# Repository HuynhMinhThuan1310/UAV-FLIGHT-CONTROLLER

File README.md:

# 🚁 UAV Quadcopter Flight Controller & Telemetry System

Hệ thống điều khiển bay (Flight Controller) và trạm thu phát dữ liệu từ xa (Ground Station) hoàn chỉnh cho máy bay không người lái (UAV Quadcopter), bao gồm đầy đủ **Phần cứng (PCB KiCad)**, **Firmware điều khiển bay (STM32CubeIDE)**, và **Firmware trạm thu dữ liệu (ESP32-C3 ESP-IDF)**.

---

## 📌 Cấu Trúc Dự Án (Repository Structure)

```text
uav_ground_station/
├── mach-UAV-main/                    # Firmware STM32CubeIDE cho máy bay
│   └── firmware/
│       ├── uav_complete_fc/          # >> Firmware điều khiển bay hoàn chỉnh (Quad Flight Controller)
│       ├── doccambien/               # Module đọc và kiểm thử cảm biến (IMU MPU6050, Khí áp, La bàn)
│       ├── DocRF/                    # Module giao tiếp vô tuyến nRF24L01+
│       └── PWM_ADC_TIMER/            # Module đọc PWM tay cầm, đo điện áp pin ADC và Timer
├── thiet_ke_mach/                    # Thiết kế phần cứng mạch PCB (KiCad 10)
│   ├── mach_uav.kicad_sch            # Sơ đồ nguyên lý (Schematic)
│   ├── mach_uav.kicad_pcb            # Mạch in hoàn chỉnh (Layout 92x92mm)
│   ├── HUONG_DAN_DI_DAY_NGOAI.md     # Sơ đồ cầu nối ngoài (W1-W6) cho mạch 1 lớp
│   ├── mach_uav-*.gbr                # Bộ file Gerber sản xuất mạch in
│   └── *.pretty / ZC323000/          # Thư viện footprint linh kiện tùy chỉnh
└── main/                             # Firmware trạm mặt đất Ground Station (ESP32-C3)
    ├── main.c                        # FreeRTOS tasks giải mã telemetry và log Serial Monitor
    ├── nrf24_rx.c / nrf24_rx.h       # Driver SPI cho nRF24L01+ ở tần số 2.480 GHz
    └── telemetry_protocol.h          # Giao thức truyền tin nhị phân 32 byte + CRC-8
```

---

## 1. Firmware Điều Khiển Bay STM32 (`mach-UAV-main/firmware/uav_complete_fc`)

Dự án phát triển trên **STM32CubeIDE** cho vi điều khiển **STM32F103C8T6 (ARM Cortex-M3 @ 72 MHz HSE)**:

- **Chế độ bay (Flight Mode):** Cố định chế độ cân bằng góc (`ANGLE Mode`) kết hợp tự động bù góc nghiêng.
- **Vòng lặp điều khiển PID:** Bộ điều khiển PID độc lập cho 3 trục Roll, Pitch, Yaw với:
  - Tích hợp bộ lọc đạo hàm (`d_filter`).
  - Khử bão hòa tích phân (Anti-windup Integrator Limit).
  - Giới hạn ngõ ra an toàn (`output_limit`).
- **Xử lý cảm biến góc nghiêng & La bàn (GY-87):**
  - Giao tiếp cảm biến `MPU6050` (Gyro + Accel) qua **Hardware I2C1 (`PB6/PB7`)** được cấu hình thanh ghi trực tiếp, tránh trễ và lỗi bus của thư viện HAL.
  - Tích hợp la bàn số `HMC5883L` sửa trôi góc Yaw theo thời gian thực (loại bỏ nhiễu từ trường khi dòng tải động cơ thay đổi đột ngột).
- **Giữ hướng bay (Heading Hold):** Khóa hướng tham chiếu (`REF`) bằng tích phân con quay hồi chuyển, duy trì mũi máy bay ổn định khi buông cần lái Yaw.
- **Đọc tín hiệu điều khiển RC (PWM Input Capture):**
  - 4 kênh PWM trên Timer `TIM3` (Roll: `PA6`, Pitch: `PA7`, Throttle: `PB0`, Yaw: `PB1`).
  - Khóa/Mở khóa động cơ bằng tổ hợp cần lái an toàn:
    - **Arm:** `Ga thấp + Gạt hết Yaw sang Phải trong 3s`.
    - **Disarm:** `Ga thấp + Gạt hết Yaw sang Trái trong 3s`.
- **Ngõ ra điều khiển động cơ (ESC Outputs):**
  - 4 kênh xung PWM độc lập (1000 - 2000 µs) trên Timer `TIM2` (`PA0`, `PA1`, `PA2`, `PA3`) bố trí theo layout quad X (`M1-M4`).
- **Cơ chế an toàn Failsafe đa cấp (`FailsafeMode`):**
  - Tự động phát hiện mất sóng vô tuyến hoặc mất xung PWM máy thu: Chuyển sang giữ thăng bằng (`HOLD`) $\rightarrow$ hạ độ cao từ từ (`DESCEND`) $\rightarrow$ phục hồi nếu có lại sóng (`RECOVER`).
  - Tự động ngắt khẩn cấp (Emergency Disarm) nếu cảm biến IMU bị lỗi liên tục.

---

## 2. Thiết Kế Mạch PCB Flight Controller (`thiet_ke_mach/`)

- **Kích thước & Thiết kế:** Bo mạch tiêu chuẩn **92 × 92 mm**, thiết kế trên **KiCad 10**.
- **Khối nguồn:** Bộ nguồn xung buck converter **MP1584EN** hạ áp từ pin LiPo cấp dòng khỏe **5V BEC**, kết hợp LDO **3.3V** riêng cho cảm biến và radio để chống sụt áp khi 4 động cơ hoạt động hết công suất.
- **Tối ưu hóa mạch 1 lớp & Giải pháp đi dây ngoài:**
  - Thiết kế mạch 1 lớp trên mặt đáy (`B.Cu`) không dùng via xuyên tầng, tối ưu cho gia công nhanh bằng phay CNC hoặc ăn mòn hóa học.
  - Định tuyến thông minh tối ưu hóa độ rộng đường mạch (Power trace 30–35 mil, Signal 14 mil, Clearance 0.20 mm).
  - Tối ưu 6 cầu nối ngoài (**W1 – W6**) có in nhãn hướng dẫn rõ ràng trực tiếp trên lớp lụa `F.SilkS` ([`HUONG_DAN_DI_DAY_NGOAI.md`](file:///C:/uav_ground_station/thiet_ke_mach/HUONG_DAN_DI_DAY_NGOAI.md)).
  - Phủ đồng mass `GND` diện tích lớn giúp tản nhiệt và chống nhiễu vô tuyến.

---

## 3. Firmware Trạm Thu Mặt Đất ESP32-C3 (`main/`)

- **Framework & RTOS:** Viết bằng native **ESP-IDF (v5.x/v6.x)** chạy trên nhân RISC-V của **ESP32-C3** với hệ điều hành thời gian thực **FreeRTOS**.
- **Giao thức Telemetry tốc độ cao (100 Hz):**
  - Gói tin nhị phân định dạng cố định **32 byte**, bảo vệ toàn vẹn bằng **CRC-8** (đa thức $0x07$).
  - Truyền nhận các khung: Góc nghiêng Roll/Pitch/Heading (`0xA1`), Vị trí cần lái RC (`0xA2`), Trạng thái vi điều khiển & chu kỳ vòng lặp PID (`0xA3`), Cân chỉnh la bàn (`0xA4`), Cấu hình PID (`0xA5`).
- **Driver vô tuyến nRF24L01+:**
  - Tần số **2.480 GHz (Kênh 80)**, tốc độ 1 Mbps, tránh hoàn toàn dải tần WiFi gia đình để thu tín hiệu ổn định.
- **Hiển thị dữ liệu qua Serial Monitor:**
  - Xuất log trực quan chu kỳ 1 giây: Tần số nhận gói (Hz), tỷ lệ mất gói (loss count), chất lượng link (%), trạng thái Arm/Failsafe, độ rộng xung 4 động cơ và góc nghiêng máy bay.

---

## 4. Hướng Dẫn Biên Dịch & Nạp Code

### 4.1 Nạp Firmware STM32 Flight Controller:
1. Mở phần mềm **STM32CubeIDE**.
2. Chọn `File` $\rightarrow$ `Open Projects from File System...` $\rightarrow$ trỏ đến thư mục `mach-UAV-main/firmware/uav_complete_fc`.
3. Kết nối mạch STM32 qua mạch nạp ST-Link (SWDIO `PA13`, SWCLK `PA14`).
4. Bấm **Build** (búa) và **Run / Flash** để nạp chương trình.

### 4.2 Nạp Firmware ESP32-C3 Ground Station:
```bash
# Đứng tại thư mục gốc uav_ground_station
idf.py set-target esp32c3
idf.py build
idf.py -p COMx flash monitor
```

---

## 5. Kỹ Năng Kỹ Thuật Đạt Được (Portfolio Highlights)

- **Lập trình Vi Điều Khiển & Nhúng Chuyên Sâu:** C/C++, ARM Cortex-M (STM32F103) trần (Bare-metal) & HAL, ESP32-C3 RISC-V với FreeRTOS.
- **Hệ Thống Điều Khiển Tự Động (Control Systems):** Thiết kế bộ điều khiển PID góc nghiêng máy bay, bộ lọc số (Digital Filter), thuật toán khóa hướng Heading Hold, xử lý an toàn Failsafe.
- **Thiết Kế Phần Cứng & PCB:** Thiết kế mạch nguyên lý, phân tách vùng nguồn số/tương tự/động lực, tính toán tiết diện đường nguồn công suất cao, thiết kế footprint trên KiCad 10.
- **Thiết Kế Mạch In & Đi Dây Tối Ưu:** Thiết kế và định tuyến mạch 1 lớp (Single-Layer PCB) không dùng via, tối ưu khoảng cách cách ly (Clearance) và độ rộng đường mạch theo dòng tải thực tế.
- **Truyền Thông Không Dây (RF Communications):** Giao thức truyền tin nhị phân tốc độ cao qua sóng 2.4 GHz nRF24L01+, kiểm tra toàn vẹn CRC-8.

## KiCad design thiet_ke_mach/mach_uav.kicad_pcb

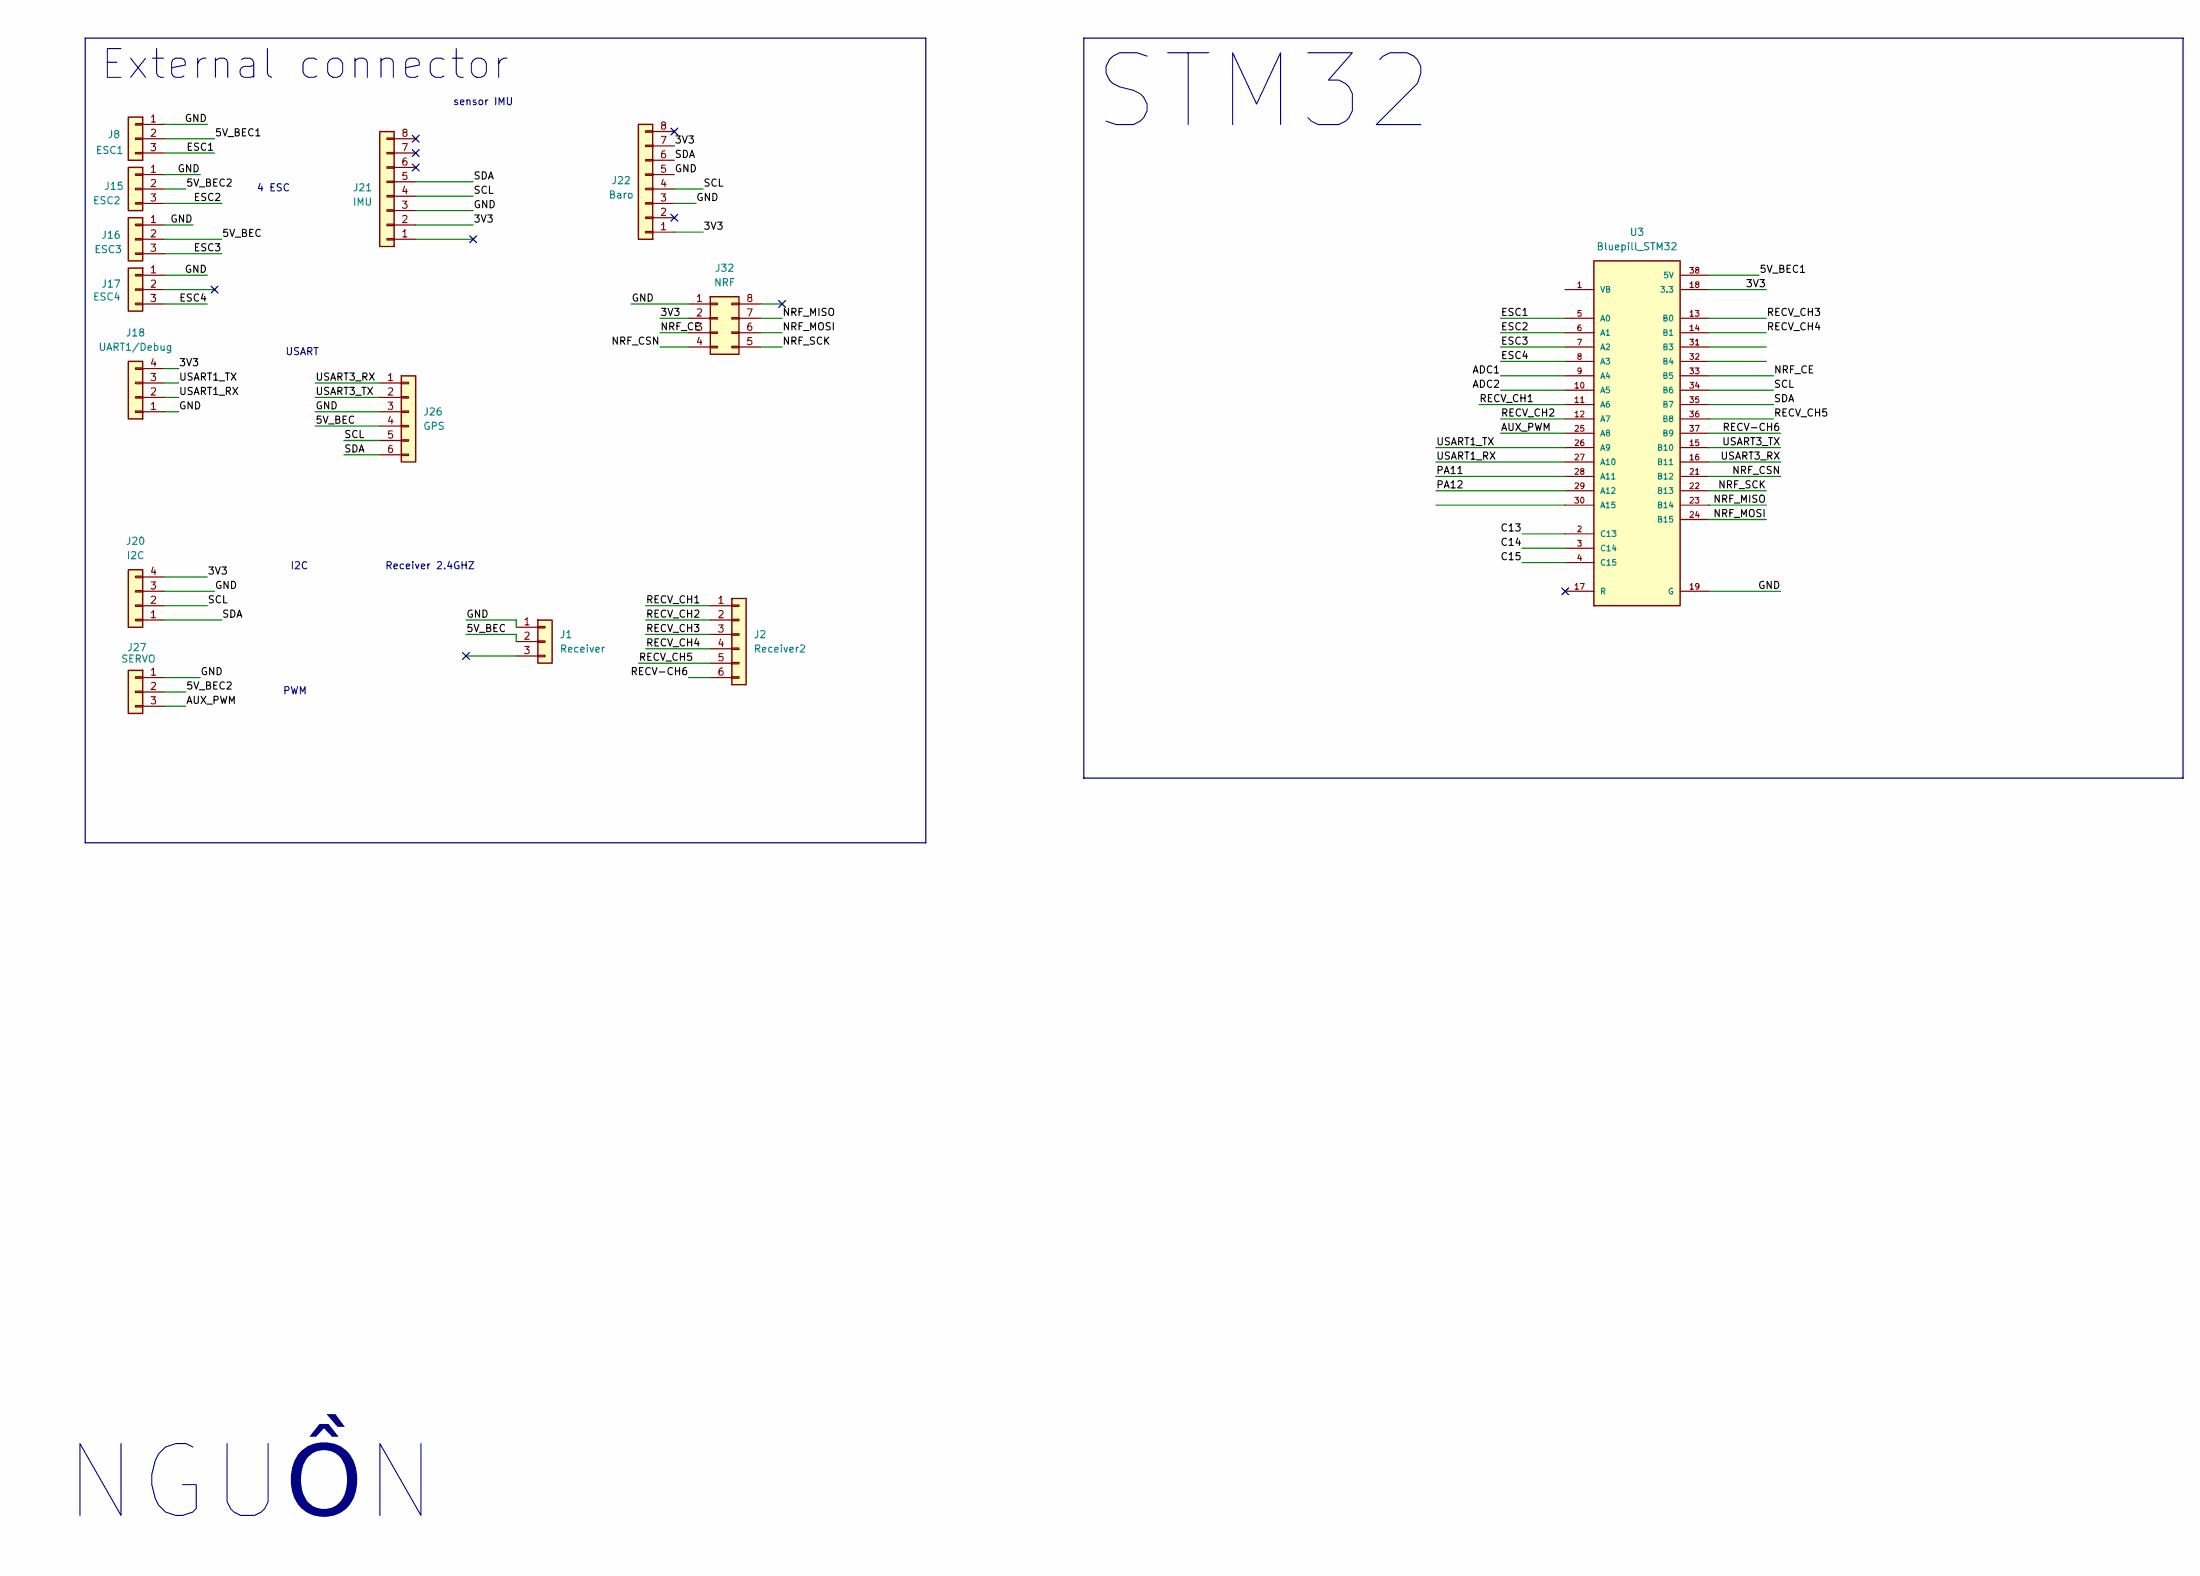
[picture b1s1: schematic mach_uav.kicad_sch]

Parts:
J1: Receiver; PinHeader_1x03_P2.54mm_Vertical
J2: Receiver2; PinHeader_1x06_P2.54mm_Vertical
J8: ESC1; PinHeader_1x03_P2.54mm_Vertical
J15: ESC2; PinHeader_1x03_P2.54mm_Vertical
J16: ESC3; PinHeader_1x03_P2.54mm_Vertical
J17: ESC4; PinHeader_1x03_P2.54mm_Vertical
J18: UART1/Debug; PinSocket_1x04_P2.54mm_Vertical
J20: I2C; PinHeader_1x04_P2.54mm_Vertical
J21: IMU; PinSocket_1x08_P2.54mm_Vertical
J22: Baro; PinSocket_1x08_P2.54mm_Vertical
J26: GPS; JST_SH_BM06B-SRSS-TB_1x06-1MP_P1.00mm_Vertical
J27: SERVO; PinHeader_1x03_P2.54mm_Vertical
J32: NRF; PinSocket_2x04_P2.54mm_Vertical
U3: Bluepill_STM32; MODULE_ZC323000; PARTREV N/A

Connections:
3.3: J18.4, J20.4, J21.2, J22.1, J22.7, J32.2, U3.18 (3.3), U3.40 (3.3)
/5V_BEC: J1.2, J16.2, J26.4
/5V_BEC1: J8.2, U3.38 (5V)
/5V_BEC2: J15.2, J27.2
/ADC1: U3.9 (A4)
/ADC2: U3.10 (A5)
/AUX_PWM: J27.3, U3.25 (A8)
/C13: U3.2 (C13)
/C14: U3.3 (C14)
/C15: U3.4 (C15)
/ESC1: J8.3, U3.5 (A0)
/ESC2: J15.3, U3.6 (A1)
/ESC3: J16.3, U3.7 (A2)
/ESC4: J17.3, U3.8 (A3)
/NRF_CE: J32.3, U3.33 (B5)
/NRF_CSN: J32.4, U3.21 (B12)
/NRF_MISO: J32.7, U3.23 (B14)
/NRF_MOSI: J32.6, U3.24 (B15)
/NRF_SCK: J32.5, U3.22 (B13)
/PA11: U3.28 (A11)
/PA12: U3.29 (A12)
/RECV-CH6: J2.6, U3.37 (B9)
/RECV_CH1: J2.1, U3.11 (A6)
/RECV_CH2: J2.2, U3.12 (A7)
/RECV_CH3: J2.3, U3.13 (B0)
/RECV_CH4: J2.4, U3.14 (B1)
/RECV_CH5: J2.5, U3.36 (B8)
/SCL: J20.2, J21.4, J22.4, J26.5, U3.34 (B6)
/SDA: J20.1, J21.5, J22.6, J26.6, U3.35 (B7)
/USART1_RX: J18.2, U3.27 (A10)
/USART1_TX: J18.3, U3.26 (A9)
/USART3_RX: J26.1, U3.16 (B11)
/USART3_TX: J26.2, U3.15 (B10)
G: J1.1, J8.1, J15.1, J16.1, J17.1, J18.1, J20.3, J21.3, J22.3, J22.5, J26.3, J27.1, J32.1, U3.19 (G), U3.20 (G), U3.39 (G)

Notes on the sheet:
USART
sensor IMU
NGUỒN
External connector
Receiver 2.4GHZ
4 ESC
STM32
I2C
PWM

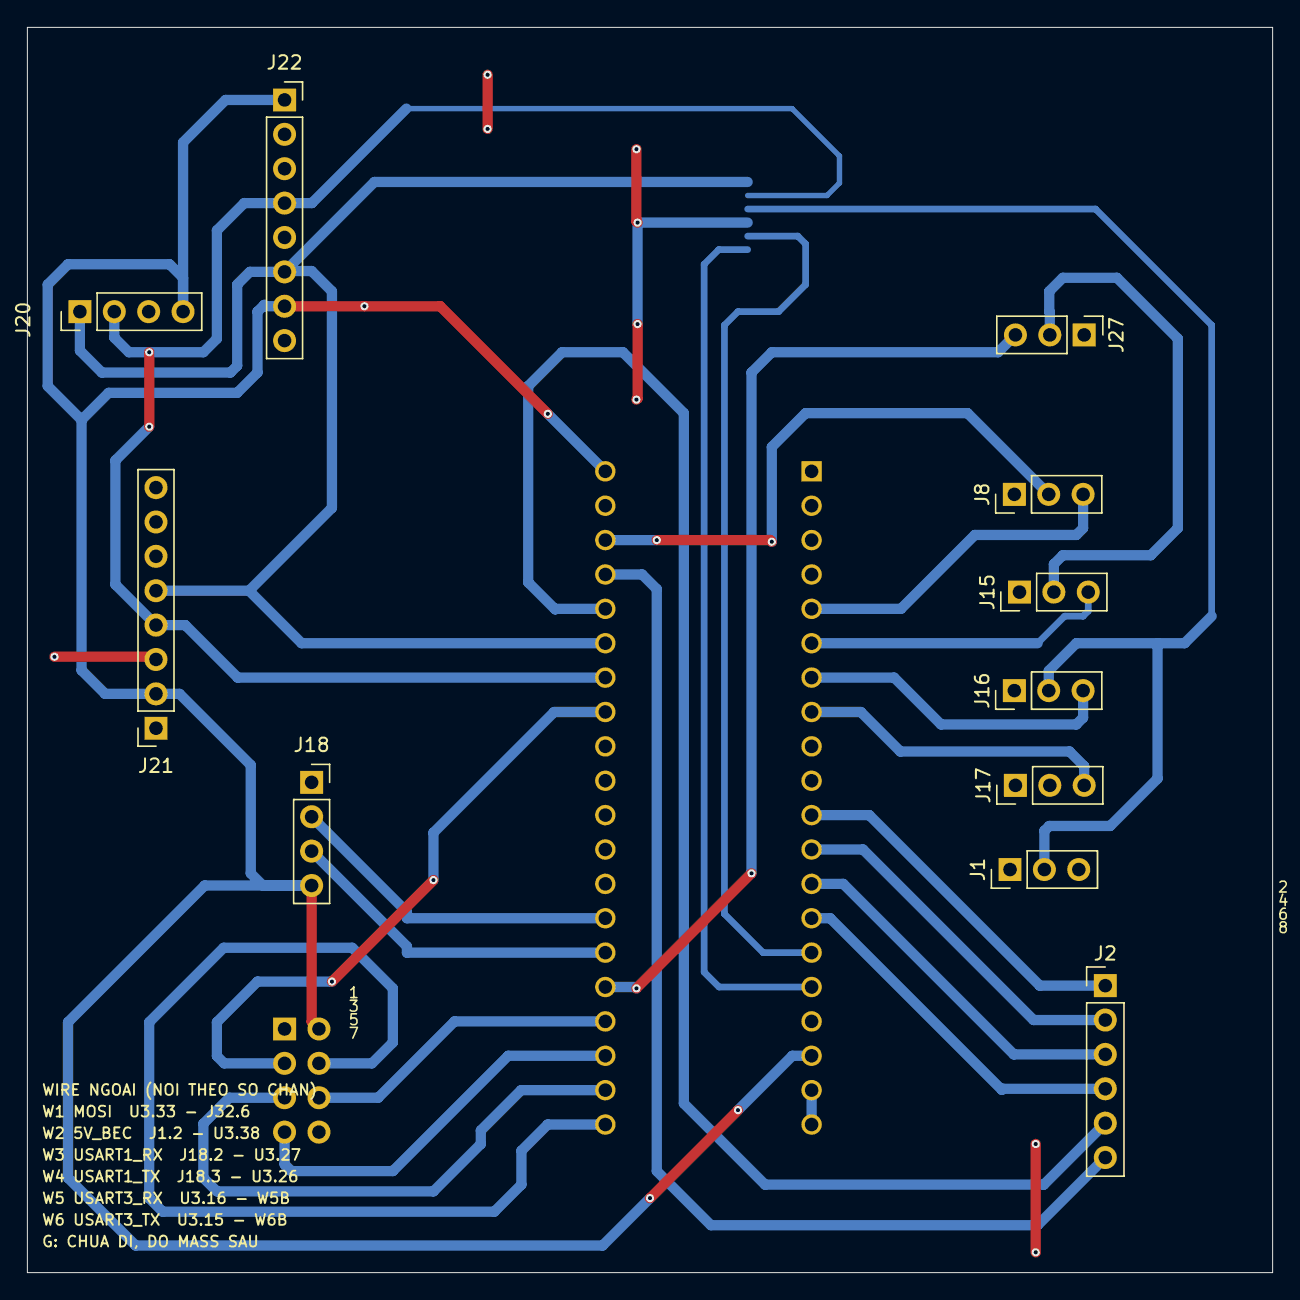
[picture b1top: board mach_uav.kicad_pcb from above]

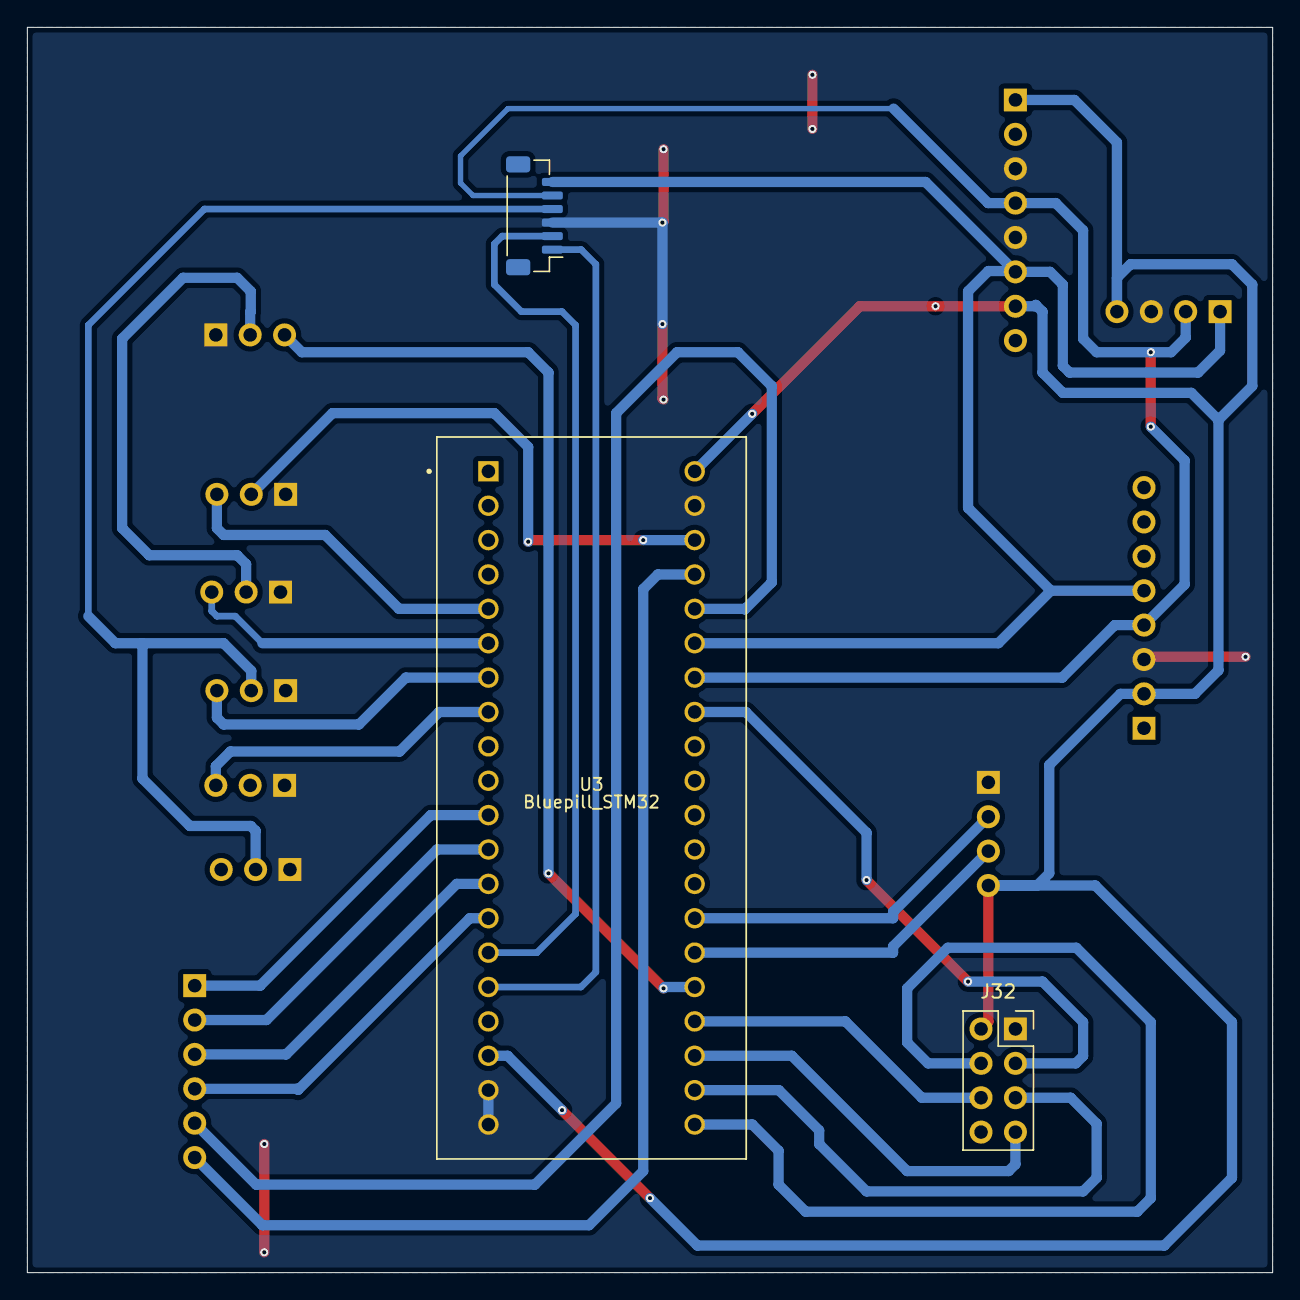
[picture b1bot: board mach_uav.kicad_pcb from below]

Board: 2 copper layers, 92.0 x 92.0 mm, 14 parts (3 on the bottom side), 27 nets.

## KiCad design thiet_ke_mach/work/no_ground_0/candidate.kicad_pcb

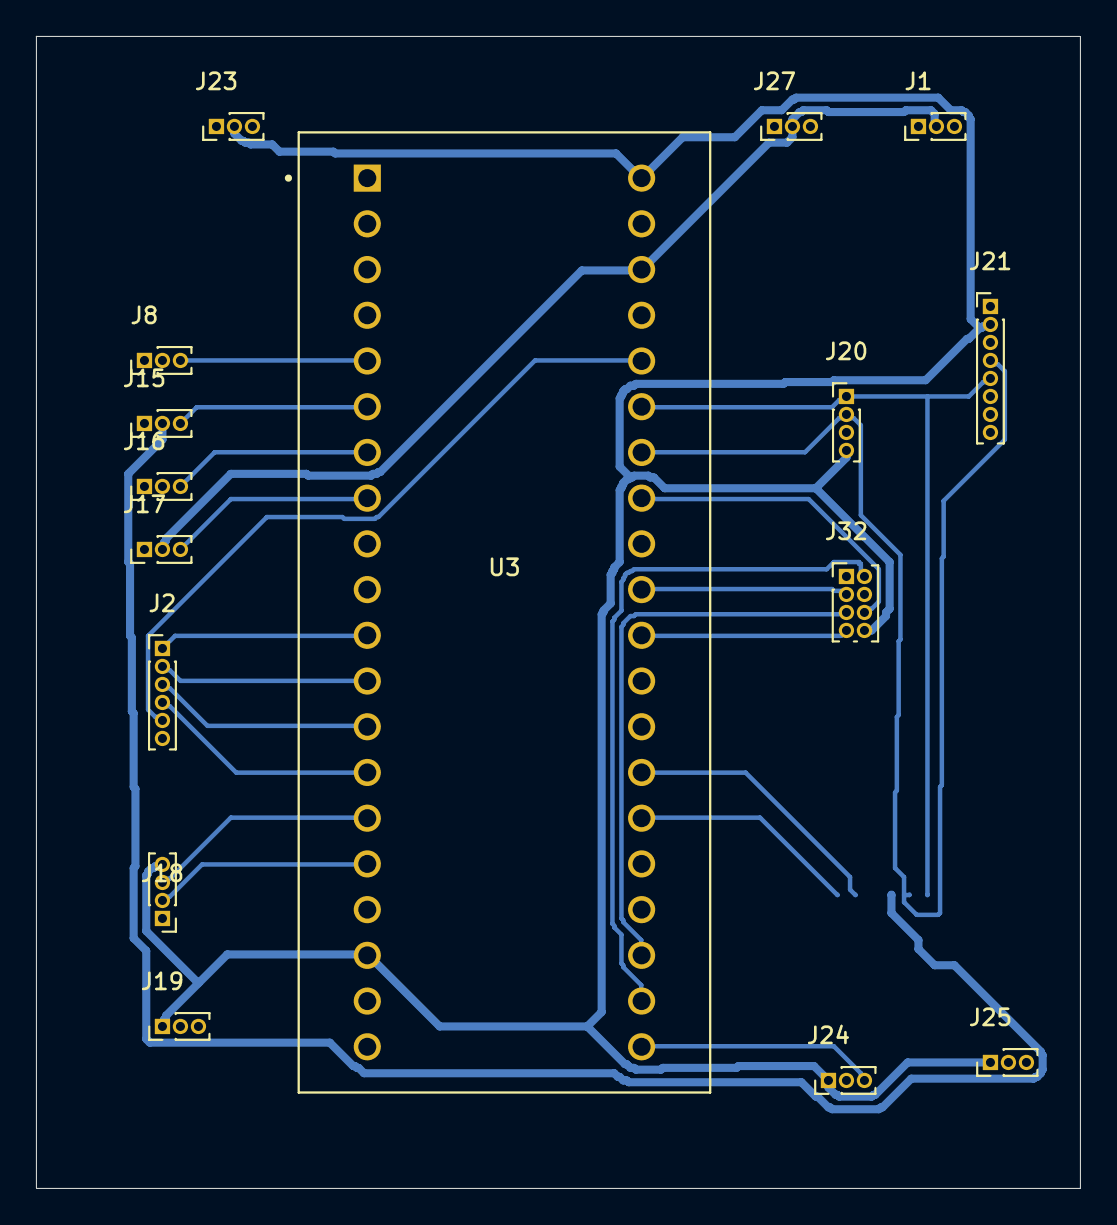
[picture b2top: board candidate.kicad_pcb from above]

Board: 2 copper layers, 58.0 x 64.0 mm, 17 parts (1 on the bottom side), 27 nets.

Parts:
J1: Receiver; PinHeader_1x03_P1.00mm_Vertical
J2: Receiver2; PinHeader_1x06_P1.00mm_Vertical
J8: ESC1; PinHeader_1x03_P1.00mm_Vertical
J15: ESC2; PinHeader_1x03_P1.00mm_Vertical
J16: ESC3; PinHeader_1x03_P1.00mm_Vertical
J17: ESC4; PinHeader_1x03_P1.00mm_Vertical
J18: UART3; PinHeader_1x04_P1.00mm_Vertical
J19: ADC0; PinHeader_1x03_P1.00mm_Vertical
J20: I2C; PinHeader_1x04_P1.00mm_Vertical
J21: IMU; PinHeader_1x08_P1.00mm_Vertical
J23: AUX_PWM; PinHeader_1x03_P1.00mm_Vertical
J24: GPIO1; PinHeader_1x03_P1.00mm_Vertical
J25: GPIO2; PinHeader_1x03_P1.00mm_Vertical
J26: GPS; JST_SH_BM06B-SRSS-TB_1x06-1MP_P1.00mm_Vertical
J27: SERVO; PinHeader_1x03_P1.00mm_Vertical
J32: NRF; PinHeader_2x04_P1.00mm_Vertical
U3: Bluepill_STM32; MODULE_ZC323000

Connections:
3.3: J18.4, J19.1, J20.4, J21.2, J23.2, J24.1, J25.1, J32.8, U3.18 (3.3), U3.40 (3.3)
/5V_BEC: J1.2, J17.2, J27.2, U3.38 (5V)
/5V_BEC1: J15.2, J26.4
/B13: J32.2, U3.22 (B13)
/B14: J32.5, U3.23 (B14)
/ESC1: J8.3, U3.5 (A0)
/ESC2: J15.3, U3.6 (A1)
/ESC3: J16.3, U3.7 (A2)
/ESC4: J17.3, U3.8 (A3)
/GPIO1: J24.3, U3.21 (B12)
/RECV-CH6: J2.6, U3.37 (B9)
/RECV_CH1: J2.1, U3.11 (A6)
/RECV_CH2: J2.2, U3.12 (A7)
/RECV_CH3: J2.3, U3.13 (B0)
/RECV_CH4: J2.4, U3.14 (B1)
/RECV_CH5: J2.5, U3.36 (B8)
/SCL: J20.2, J21.4, J26.5, U3.34 (B6)
/SDA: J20.1, J21.5, J26.6, U3.35 (B7)
/SPI1_CS: J32.7, U3.30 (A15)
/SPI1_MISO: J32.4, U3.32 (B4)
/SPI1_MOSI: J32.6, U3.33 (B5)
/SPI1_SCK: J32.3, U3.31 (B3)
/USART1_RX: J26.2, U3.27 (A10)
/USART1_TX: J26.1, U3.26 (A9)
/USART3_RX: J18.2, U3.16 (B11)
/USART3_TX: J18.3, U3.15 (B10)
G: J1.1, J8.1, J15.1, J16.1, J17.1, J18.1, J19.2, J20.3, J21.3, J23.1, J24.2, J25.2, J26.3, J27.1, J32.1, U3.19 (G), U3.20 (G), U3.39 (G)
